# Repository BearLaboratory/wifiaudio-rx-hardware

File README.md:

<h1 align="center" style="font-size:50px;font-weight:bold">WiFiAudio</h1>
<p align="center">基于WiFi的语音传输系统</p>
<p align="center">

</p>

整个系统在组织下分为及个仓库，请根据个人的需求参考：
- [语音发射端硬件](https://github.com/BearLaboratory/wifiaudio-tx-hardware)
- [发射端固件](https://github.com/BearLaboratory/wifiaudio-tx-firmware)
- [接收端硬件](https://github.com/BearLaboratory/wifiaudio-rx-hardware)
- [接收端固件](https://github.com/BearLaboratory/wifiaudio-rx-firmware)
- [PC端接收服务](https://github.com/BearLaboratory/wifiaudio-rx-pc)
- [PCM5102A解码验证模块](https://github.com/BearLaboratory/esp32-pcm51202-audio-hardware)

整个系统所使用的到的工具；
- [EDA工具使用开源免费的Kicad](https://www.kicad.org/)
- [固件开发使用简单的Arduino](https://www.arduino.cc/)

# 1. WiFi Audio RX （基于WiFi的无线麦克风接收端硬件）

WiFi Audio项目的目的是DIY一个开源且便宜的无线麦克风，辅助自己在拍摄视频时的收音。项目有几个根本点：
- 软件键全开源，方便大家对软硬件部分进行针对性的修改；
- 整体成本尽量低，为了达到这个目的在硬件设计部分，我舍弃了很多锦上添花的硬件（比如屏幕）；
- 基于WiFi，由于我个人想让麦克风能接入网络，因此抛弃了传统的UHF转而投入了WiFi的怀抱，正巧这两年芯片价格飞涨唯一还算正常的是上来乐鑫的ESP32系列芯片，价格便宜功能强大具有WiFi及蓝牙功能，因此选择它作为我们麦克的核心处理芯片。

麦克风选择我直接抛弃了传统模拟麦克风，虽然价格便宜，但是其外围电路较复杂，电路对声音音质的影响较大，不适合我们DIY。麦克风我测试的有两款一个是inmp441另一款是ics43434，后者是前者的替代品拥有更高的信噪比，我个人十分推荐使用ics43434。当然还有其他麦克风，奈何我自己没有买来测试，如果有小伙伴有自行测试，请将测试结果反馈给我 <mail>dengyi@dengyi.pro</mail>

# 2. 如何自行打板

整个硬件部分已完整打板测试，如果你使用嘉立创下单助手，直接将gebber目录下压缩文件上传即可，我推荐板材厚度选择1,1.6厚度过大，平时自己焊接过程中加热较麻烦。

如果你使用嘉立创smt服务时，上传坐标文件及bom_lc bom清单即可，如果出现错误，你需要手动去调整原件的方向等，确保焊盘准确即可，bom本身无任何问题。

# 2. 如何上传固件

固件部分，请参考其他仓库。对于固件我都是使用arduino进行编写，因此你需要安装arduino IDE，然后克隆固件仓库，然后进行编译上传。

需要特殊说明：因为我想尽量控制设备成本，所以没有板载烧录电路。进行固件的烧写需要使用我之前开发的ESP系列芯片烧录工具，具体的信息请参见这个仓库[ESP系列芯片烧录工具](https://github.com/BearLaboratory/downloader)

# 3. 如何使用

对于如何使用这部分，我推荐大家反复观看我的项目视频。因为我个人精力有限，每次readme文档我都写的比较糙（虽然多次召集负责写readme的小伙伴，但是并未成功）
# 4. 其他

整个项目在GPL协议下开源，禁止商用，商用请联系<mail>dengyi@dengyi.pro</mail>。

组织下所有开源项目均为个人出于兴趣进行开发及维护，并没有任何盈利，所以在维护频率上可能有很大的延迟，如果小伙伴们有兴趣可以发送邮件到<mail>dengyi@dengyi.pro</mail>与我个人联系或参与到开发中。同时非常欢迎对我的视频频道进行点赞或者关注，[B站](https://space.bilibili.com/402729300),[知乎](https://www.zhihu.com/people/deng-yi-92-16/columns),[youtube](https://www.youtube.com/channel/UCXvLKESzLbINYVe9J8rXerQ)

硬件可以个人自行在嘉立创下单打板，如果需要成品请直接在咸鱼搜索用户**BLab大熊实验室**，由于是非职业卖家，快递费由系统自行计算我做不了主还请谅解。

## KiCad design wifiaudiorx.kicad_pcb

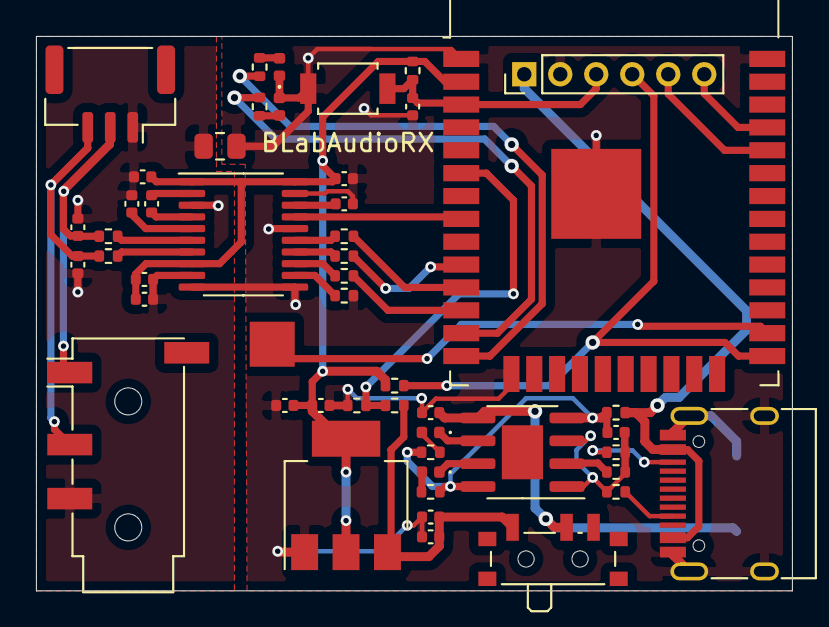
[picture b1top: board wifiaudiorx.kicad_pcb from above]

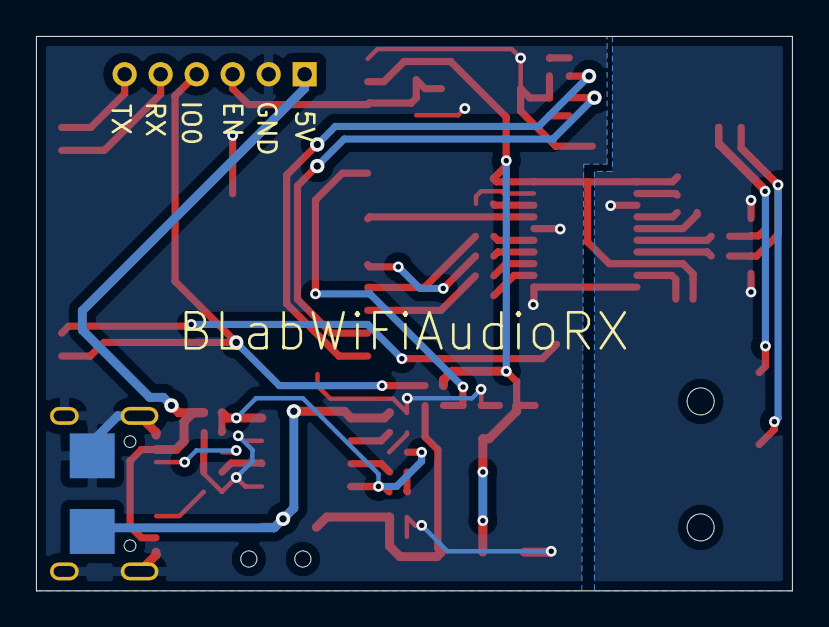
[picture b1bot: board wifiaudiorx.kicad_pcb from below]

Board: 2 copper layers, 42.0 x 30.8 mm, 52 parts (2 on the bottom side), 40 nets.

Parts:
C1: 1uf; C_0402_1005Metric
C2, C7, C8, C9, C10, C15: 0.1uf; C_0402_1005Metric
C3, C4, C5, C6, C11: 10uf; C_0402_1005Metric
C12, C13: 2.2nf; C_0402_1005Metric
C14, C16: 2.2uf; C_0402_1005Metric
D1: LED-red; D_0402_1005Metric
D2, D3, D4: LED-green; D_0402_1005Metric
J1: AudioJack4; Jack_3.5mm_PJ320D_Horizontal
J2: Conn_01x03_Female; JST_GH_SM03B-GHS-TB_1x03-1MP_P1.25mm_Horizontal
J4, J5, J7: Conn_01x01_Female; largepoint
J6: USB_C_Receptacle_USB2.0; USB_C_Receptacle_HRO_TYPE-C-31-M-12
J8: Conn_01x06_Female; PinHeader_1x06_P2.00mm_Vertical
R1, R2: 5.1k; R_0402_1005Metric
R3, R4, R17, R18: 10k; R_0402_1005Metric
R5: 0.4; R_0402_1005Metric
R6, R8, R15, R16: 1k; R_0402_1005Metric
R7: 1.2k; R_0402_1005Metric
R9, R10, R11, R12, R13, R19: 470; R_0402_1005Metric
R14: 0; R_0805_2012Metric
SW1: SW_DPDT_x2; SW_SPDT_PCM12
SW2: SW_Push; bt-342
U1: ESP-32S; ESP32-WROOM-32
U2: pcm5102a; TSSOP-20_4.4x6.5mm_P0.65mm
U3: tp4056; SOIC-8-1EP_3.9x4.9mm_P1.27mm_EP2.29x3mm
U4: AMS1117-3.3; SOT-223-3_TabPin2

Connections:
+3V3: C3.1, C7.1, C8.2, C9.1, C10.1, C11.2, R3.1, R4.2, U1.2, U2.1, U2.8, U2.20, U4.2
+5V: J6.A4, J6.A9, J6.B4, J6.B9, J8.1, R5.2
ADC: R17.2, R18.1, U1.6
BAT: C5.1, J4.1, SW1.2, U3.5
BCK: R9.1, U1.12
DOUT: R10.2, U1.10
EN: C1.1, J8.3, R3.2, SW2.2, U1.3
GND: C1.2, C2.2, C3.2, C4.2, C5.2, C6.2, C7.2, C10.2, C15.1, D3.1, D4.1, J5.1, J6.A1, J6.A12, J6.B1, J6.B12, J6.S1, J8.2, R1.1, R2.1, R7.2, R14.1, R17.1, R19.1, SW2.1, U1.1, U1.15, U1.38, U1.39, U2.10, U2.11, U2.16, U2.19, U3.1, U3.3, U4.1
GNDA: C8.1, C9.2, C11.1, C12.1, C13.1, C16.2, J1.R2, J2.1, R14.2, U2.3, U2.9
IO0: J8.4, R4.1, U1.25
LRCK: R11.1, U1.11
MUTE: U1.8, U2.17
unnamed: C2.1, C6.1, R18.2, SW1.1, U4.3
unnamed: C4.1, R5.1, R6.2, R8.2, U3.4, U3.8
unnamed: C14.1, U2.2
unnamed: C14.2, U2.4
unnamed: C15.2, U2.18
unnamed: C16.1, U2.5
unnamed: D1.1, U3.7
unnamed: D1.2, R6.1
unnamed: D2.1, U3.6
unnamed: D2.2, R8.1
unnamed: D3.2, R15.1
unnamed: D4.2, R16.1
unnamed: J6.A5, R1.2
unnamed: J6.B5, R2.2
unnamed: J7.1, U1.26
unnamed: R7.1, U3.2
unnamed: R9.2, U2.13
unnamed: R10.1, U2.14
unnamed: R11.2, U2.15
unnamed: R12.1, U2.6
unnamed: R13.1, U2.7
unnamed: R15.2, U1.13
unnamed: R16.2, U1.14
unnamed: R19.2, U2.12
OL: C12.2, J1.T, J2.2, R12.2
OR: C13.2, J1.R1, J2.3, R13.2
RXD: J8.5, U1.34
TXD: J8.6, U1.35

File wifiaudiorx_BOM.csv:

"Comment","Description","Designator","Footprint","LibRef","Pins","Quantity","PartNumber","url",
"1uf","desc","C1,","C_0402_1005Metric","libref","2","1","","",
"2.2nf","desc","C13,C12,","C_0402_1005Metric","libref","2","2","","",
"2.2uf","desc","C16,C14,","C_0402_1005Metric","libref","2","2","","",
"10uf","desc","C5,C4,C6,C3,C11,","C_0402_1005Metric","libref","2","5","","",
"0.1uf","desc","C7,C2,C15,C10,C9,C8,","C_0402_1005Metric","libref","2","6","","",
"LED-red","desc","D1,","D_0402_1005Metric","libref","2","1","","",
"LED-green","desc","D4,D3,D2,","D_0402_1005Metric","libref","2","3","","",
"Conn_01x03_Female","desc","J2,","JST_GH_SM03B-GHS-TB_1x03-1MP_P1.25mm_Horizontal","libref","5","1","","",
"Conn_01x01_Female","desc","J7,","largepoint","libref","1","1","","",
"0","desc","R14,","R_0805_2012Metric","libref","2","1","","",
"1k","desc","R16,R15,R8,R6,","R_0402_1005Metric","libref","2","4","","",
"470","desc","R19,R12,R13,R11,R10,R9,","R_0402_1005Metric","libref","2","6","","",
"5.1k","desc","R2,R1,","R_0402_1005Metric","libref","2","2","","",
"10k","desc","R4,R3,R18,R17,","R_0402_1005Metric","libref","2","4","","",
"0.4","desc","R5,","R_0402_1005Metric","libref","2","1","","",
"1.2k","desc","R7,","R_0402_1005Metric","libref","2","1","","",
"SW_Push","desc","SW2,","bt-342","libref","2","1","","",
"ESP-32S","desc","U1,","ESP32-WROOM-32","libref","39","1","","",
"pcm5102a","desc","U2,","TSSOP-20_4.4x6.5mm_P0.65mm","libref","20","1","","",
"tp4056","desc","U3,","SOIC-8-1EP_3.9x4.9mm_P1.27mm_EP2.29x3mm","libref","13","1","","",
"AMS1117-3.3","desc","U4,","SOT-223-3_TabPin2","libref","4","1","","",
"Conn_01x01_Female","desc","J5,J4,","largepoint","libref","1","2","","",
"Through Hole Items ",
"AudioJack4","desc","J1,","Jack_3.5mm_PJ320D_Horizontal","libref","6","1","","",
"USB_C_Receptacle_USB2.0","desc","J6,","USB_C_Receptacle_HRO_TYPE-C-31-M-12","libref","22","1","","",
"Conn_01x06_Female","desc","J8,","PinHeader_1x06_P2.00mm_Vertical","libref","6","1","","",
"SW_DPDT_x2","desc","SW1,","SW_SPDT_PCM12","libref","9","1","","",

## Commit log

2021-12-02 init
2021-12-02 add bom lc
2021-12-02 修改readme
2021-12-02 Create LICENSE

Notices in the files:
README.md:
GPL License
